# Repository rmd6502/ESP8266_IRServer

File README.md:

ESP8266 IR Throwie
==================

This takes the concept of the TV-B-Gone one step further
by allowing the device to be controlled with Wifi.

This version hardcodes the wifi parameters, but a future version
will allow use as an Access Point to set up wifi.

You'll need [my fork](https://github.com/rmd6502/IRremoteESP8266) of the IRRemote ESP8266 
library for the Dyson remote protocol support.

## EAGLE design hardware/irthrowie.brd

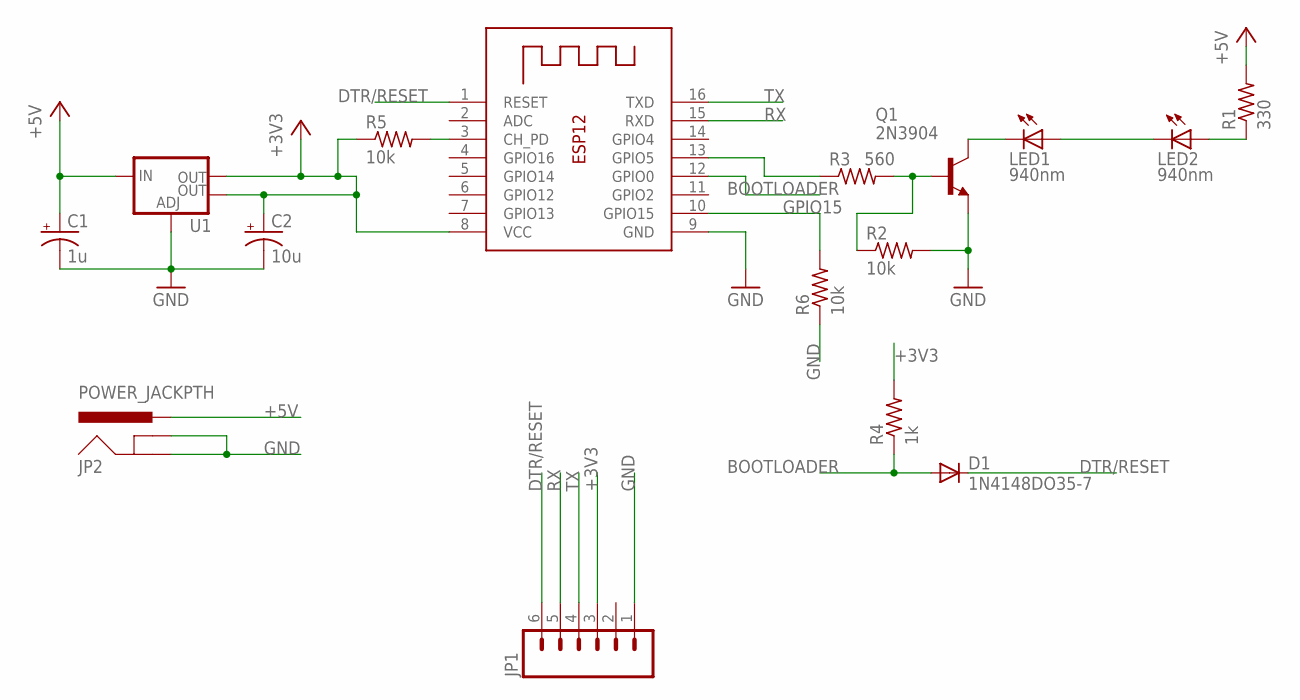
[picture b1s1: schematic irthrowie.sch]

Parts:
C1: 1u; PANASONIC_B
C2: 10u; PANASONIC_B
D1: 1N4148DO35-7; DO35-7
JP1: M06LOCK; 1X06_LOCK
JP2: POWER_JACKPTH; POWER_JACK_PTH
LED1, LED2: 940nm; LED5MM
Q1: 2N3904; TO92
R1: 330; 0204/7
R2, R5, R6: 10k; 0204/7
R3: 560; 0204/7
R4: 1k; 0204/7
U1: V_REG_LM1117SOT223; SOT223
X1: ESP-12

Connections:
+3V3: C2.+, JP1.3, R4.2, R5.1, U1.2 (OUT), U1.4 (OUT), X1.8 (VCC)
+5V: C1.+, JP2.PWR, R1.2, U1.3 (IN)
BOOTLOADER: D1.A, R4.1, X1.12 (GPIO0)
DTR/RESET: D1.C, JP1.6, X1.1 (RESET)
GND: C1.-, C2.-, JP1.1, JP2.GND, JP2.GNDBREAK, Q1.3 (E), R2.2, R6.1, U1.1 (ADJ), X1.9 (GND)
GPIO15: R6.2, X1.10 (GPIO15)
unnamed: LED1.A, LED2.K (C)
unnamed: Q1.2 (B), R2.1, R3.2
unnamed: LED1.K (C), Q1.1 (C)
unnamed: LED2.A, R1.1
unnamed: R5.2, X1.3 (CH_PD)
unnamed: R3.1, X1.13 (GPIO5)
RX: JP1.5, X1.15 (RXD)
TX: JP1.4, X1.16 (TXD)

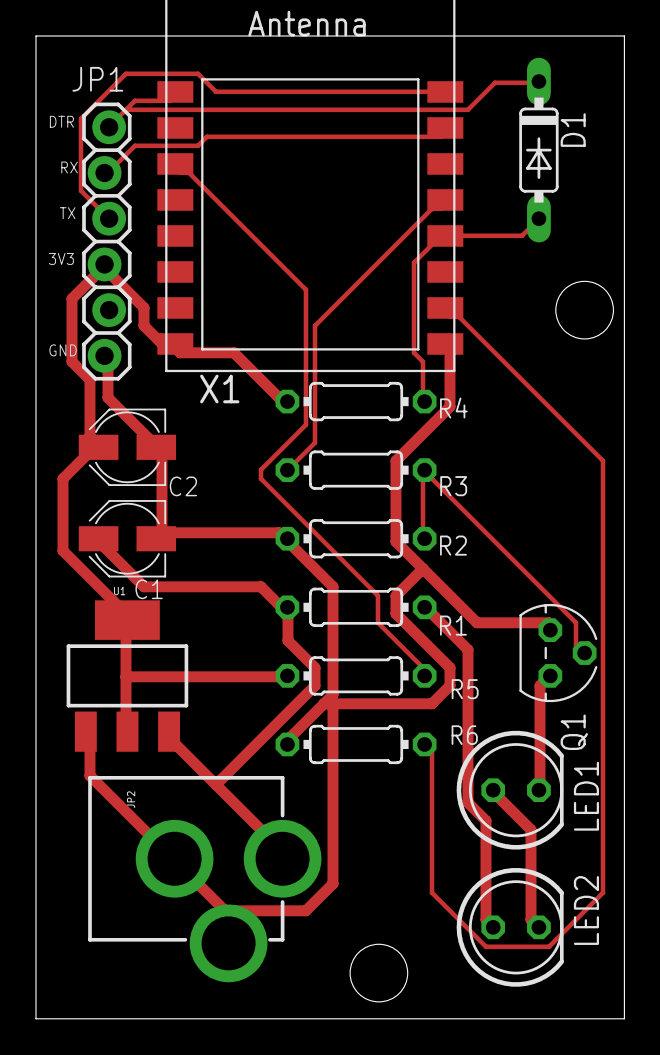
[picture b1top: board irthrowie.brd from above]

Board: 2 copper layers, 32.7 x 54.6 mm, 16 parts (0 on the bottom side), 14 nets.

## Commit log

2016-02-01 first rev
2016-02-01 add readme
2016-02-01 add case design
2016-02-02 add schematic
2016-02-02 add png image

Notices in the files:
parts and their libraries:
SparkFun-Connectors: Licensing: Creative Commons ShareAlike 4.0 International - https://creativecommons.org/licenses/by-sa/4.0
